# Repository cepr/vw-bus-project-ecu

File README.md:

# vw-bus-project-ecu
ECU based on Speeduino for my VW Bus project

# Licenses
The schematics and layout are under the TAPR Open Hardware License v1.0

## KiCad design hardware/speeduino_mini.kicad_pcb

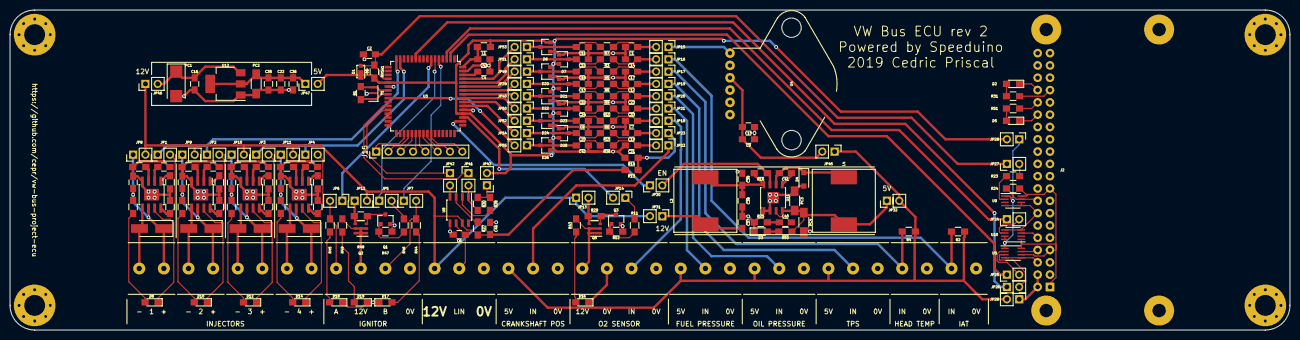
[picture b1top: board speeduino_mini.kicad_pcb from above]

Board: 2 copper layers, 264.2 x 66.0 mm, 209 parts (0 on the bottom side), 147 nets.

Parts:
C1: 0.47nF 50V; C_0805_HandSoldering
C2: 4.7nF 100V; C_0805_HandSoldering
C4, C7, C12, C14, C16, C17, C19, C21, C22, C23, C33, C35, C36, C43: 0.1uF 50V; C_0805_HandSoldering
C6: 0.22nF 200V; C_0805_HandSoldering
C8, C13, C15, C18, C20, C32, C34, C41, C42: 0.22uF 50V; C_0805_HandSoldering
C9, C39, C46: 1uF 35V; C_0805_HandSoldering
C10: 10nF 100V; C_0805_HandSoldering
C11: 0.33uF 50V; C_0805_HandSoldering
C24, C26, C28, C30: 1nF 50V; C_0805_HandSoldering
C25, C27, C29, C31: 22uF 16V; C_0805_HandSoldering
C37, C38: 22uF 25V; C_0805_HandSoldering
C40: 22nF 50V; C_0805_HandSoldering
D1: MSS1P3L-M3/89A; MicroSMP
D2, D17, D18: LED BLUE 10mA 3V; LED_0805_HandSoldering
D3, D16, D19: LED GREEN 2.5mA 2.7V; LED_0805_HandSoldering
D4: D_Schottky; D_SOD-123F
D5, D8, D10, D12, D14: LED RED 10mA 1.9V; LED_0805_HandSoldering
D6, D7, D20, D21, D22, D23, D24, D25, D26: NUP1301,215; SOT-23
D9, D11, D13, D15: B340A-13-F; D_SMA_Handsoldering
H1, H2, H3, H4: MountingHole; MountingHole_4.3mm_M4_Pad_Via
J1: O2; ED120_4DS
J2: Raspberry_Pi_2_3; RaspberryPi_uHAT
J3: TPS; ED120_3DS
J4: IAT; ED120_2DS
J5: head temperature; ED120_2DS
J6: crankshaft position sensor; ED120_3DS
J7, J8, J9, J10: Injector; ED120_2DS
J11: Ignitor Pack; ED120_4DS
J12: oil pressure; ED120_3DS
J13: fuel pressure; ED120_3DS
J14: power; ED120_3DS
J15: Conn_01x08_Female; Pin_Header_Straight_1x08_Pitch2.54mm
JP1, JP2, JP3, JP4, JP5, JP6, JP7, JP8, JP9, JP10, JP11, JP12, JP13, JP14, JP15, JP16, JP17, JP18, JP19, JP20, JP21, JP22, JP23, JP24, JP25, JP26, JP27, JP28, JP29, JP30, JP31, JP32, JP39, JP40, JP41, JP42, JP43, JP45, JP46, JP47, JP49, JP50, JP51, JP52, JP53, JP54, JP55: Jumper; Pin_Header_Straight_1x02_Pitch2.54mm
L1: 10uH; L_0805_HandSoldering
L3, L4: 47uH; BOURNS_SRR1260
PC1: 47uF; CP_Tantalum_Case-C_EIA-6032-28_Reflow
PC2, PC3, PC4: 47uF 10V; C_1206_HandSoldering
Q1, Q3: 2N7002; SOT-23
Q2, Q5: SQ3457EV; TSOP-6_1.65x3.05mm_Pitch0.95mm
R1: 1M; R_0805_HandSoldering
R2, R4: 2.49k; R_0805_HandSoldering
R3, R5, R6, R8, R9, R10, R15, R26: 470; R_0805_HandSoldering
R7: 750; R_0805_HandSoldering
R11, R23, R46: 150; R_0805_HandSoldering
R12, R16, R17, R21, R24, R29, R35, R39, R47, R48: 10k; R_0805_HandSoldering
R13: 3.9k; R_0805_HandSoldering
R14, R19, R33, R37, R41: 1k; R_0805_HandSoldering
R18, R22, R36, R40: 47.5k; R_0805_HandSoldering
R20, R34, R38, R42: 26.1k; R_0805_HandSoldering
R25: 22k; R_0805_HandSoldering
R27, R28: 33k; R_0805_HandSoldering
R30: 4k7; R_0805_HandSoldering
R31, R44, R45: 200; R_0805_HandSoldering
R43, R49: 3.74k; R_0805_HandSoldering
R50: 910; R_0805_HandSoldering
R51: 309; R_0805_HandSoldering
RN5A1: 10k; R_0805_HandSoldering
U3: ATmega2561-16AU; TQFP-64_14x14mm_Pitch0.8mm
U4: MPX4250AP1; xP_01ASB0907B
U5, U9, U10: SN74LVC2T45MDCTTEP; SSOP-8_2.95x2.8mm_Pitch0.65mm
U7, U13, U14, U15: DRV103H; TI_SO-PowerPAD-8
U8: MCP2003B; SOIC-8_3.9x4.9mm_Pitch1.27mm
U11: TLE8366; SOIC-8-1EP_3.9x4.9mm_Pitch1.27mm
U12: LD1117S50TR_SOT223; SOT-223-3_TabPin2
Y1: CSTCE16M0V53-R0; Resonator_SMD_Murata-3pin_3.2x1.3mm

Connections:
+5VA: J3.1, J6.1, J12.1, J13.1, JP29.2, JP32.2, JP45.1, R2.1, R4.1
+5VD: D1.1, D6.2, D7.2, D20.2, D21.2, D22.2, D23.2, D24.2, D25.2, D26.2, JP28.2, JP43.2, JP47.2, L1.1, RN5A1.1, U3.21, U3.52
+12V: C46.1, J14.1, JP8.2, JP9.2, JP10.2, JP11.2, JP12.2, JP13.1, JP31.2, JP46.1, R13.1, R27.2, U8.7
/Crankshaft pos sensor/IN: J6.2, JP22.1
/Fuel Pressure/IN: J13.2, JP21.1
/Head Temperature Sensor/IN: J5.1, JP17.1, R4.2
/Ignitor/+12V: JP12.1, Q2.4, R48.1
/Ignitor/EN: JP5.2, R46.2
/Ignitor/IN1: J11.1, JP6.2, R45.2
/Ignitor/IN2: J11.3, JP7.2, R44.2
/Ignitor/sheet5CF8D1B3/OUT: J11.2, Q2.1, Q2.2, Q2.5, Q2.6, R49.2
/Injector 1/+12V: C25.1, D9.1, J7.1, JP8.1, R19.1, U7.6
/Injector 1/INJ_CMD: JP1.2, R17.1, U7.8
/Injector 2/+12V: C27.1, D11.1, J8.1, JP9.1, R33.1, U13.6
/Injector 2/INJ_CMD: JP2.2, R21.1, U13.8
/Injector 3/+12V: C29.1, D13.1, J9.1, JP10.1, R37.1, U14.6
/Injector 3/INJ_CMD: JP3.2, R35.1, U14.8
/Injector 4/+12V: C31.1, D15.1, J10.1, JP11.1, R41.1, U15.6
/Injector 4/INJ_CMD: JP4.2, R39.1, U15.8
/Intake Air Temperature Sensor/IN: J4.1, JP16.1, R2.2
/MAP Sensor/+5V: C9.1, C10.1, JP45.2, U4.3
/MCU/A0: C11.1, D6.3, JP53.1, R7.1
/MCU/A1: C15.1, D7.3, JP51.1, R3.1
/MCU/A2: C18.1, D20.3, JP49.1, R5.1
/MCU/A3: C13.1, D21.3, JP39.1, R8.1
/MCU/A4: C32.1, D22.3, JP40.1, R9.1
/MCU/A5: C34.1, D23.3, JP50.1, R10.1
/MCU/A6: C8.1, D24.3, JP52.1, R6.1
/MCU/A7: C20.1, D25.3, JP54.1, R15.1
/MCU/ATMEGA regulator/AVCC: C43.1, L1.2, U3.64
/MCU/INT0: C42.1, D26.3, JP55.1, R26.1
/MCU/LIN: C6.1, J14.2, U8.6
/MCU/OC1A: JP3.1, JP4.1, U3.15
/MCU/OC1B: JP1.1, JP2.1, U3.16
/MCU/OC3A: JP7.1, U3.5
/MCU/OC3B: JP5.1, U3.6
/MCU/OC3C: JP6.1, U3.7
/MCU/PA0: JP14.2, U3.51
/MCU/PA1: JP30.1, U3.50
/MCU/RESET: C2.1, D1.2, JP27.1, RN5A1.2, U3.20
/MCU/RXD0: JP25.1, U3.2
/MCU/SCK: JP26.1, U3.11
/MCU/TXD0: JP24.1, U3.3
/MCU/sheet5D16F277/+5V: JP43.1, R28.2, R30.1
/MCU/sheet5D16F277/RXD: JP41.2, R30.2, U8.1
/MCU/sheet5D16F277/TXD: JP42.2, U8.4
/O2 Sensor Power/+12V: JP13.2, Q5.4, R29.1
/O2 Sensor Power/EN: JP14.1, R11.2
/O2 Sensor Power/OUT: J1.1, Q5.1, Q5.2, Q5.5, Q5.6, R43.2
/O2 Sensor/IN: J1.3, JP18.1
/Oil Pressure Sensor/IN: J12.2, JP20.1
/Power/+5V: JP32.1, L4.2, PC3.1, PC4.1, R50.2, U11.4
/Power/+12V: C37.1, JP31.1, L3.1
/Power/EN: JP30.2, R16.1, U11.7
/Raspberry Pi Zero W/+5VA: J2.2, J2.4, JP29.1
/Raspberry Pi Zero W/+5VD: JP28.1, U5.1, U9.1, U10.7, U10.8
/Raspberry Pi Zero W/ATMEGA_RESET: JP27.2, R23.2
/Raspberry Pi Zero W/RXD_PDO: JP24.2, U10.6
/Raspberry Pi Zero W/SCK: JP26.2, U5.3
/Raspberry Pi Zero W/TXD_PDI: JP25.2, U5.2
/Throttle Position Sensor /IN: J3.2, JP19.1
GND: C1.2, C2.2, C4.2, C6.2, C7.2, C8.2, C9.2, C10.2, C11.2, C12.2, C13.2, C14.2, C15.2, C16.2, C17.2, C18.2, C19.2, C20.2, C21.2, C22.2, C23.2, C24.2, C25.2, C26.2, C27.2, C28.2, C29.2, C30.2, C31.2, C32.2, C33.2, C34.2, C35.2, C36.2, C37.2, C38.2, C39.2, C42.2, C43.2, C46.2, D2.1, D3.1, D4.2, D5.1, D6.1, D7.1, D16.1, D17.1, D18.1, D19.1, D20.1, D21.1, D22.1, D23.1, D24.1, D25.1, D26.1, J1.2, J1.4, J2.6, J2.14, J2.20, J2.30, J2.34, J3.3, J4.2, J5.2, J6.3, J11.4, J12.3, J13.3, J14.3, PC1.2, PC2.2, PC3.2, PC4.2, Q1.2, Q3.2, R12.2, R14.2, R17.2, R18.2, R20.2, R21.2, R22.2, R25.2, R34.2, R35.2, R36.2, R38.2, R39.2, R40.2, R42.2, R47.2, U3.22, U3.53, U3.63, U4.2, U5.4, U5.5, U7.4, U7.9, U8.5, U9.4, U9.5, U9.6, U10.4, U10.5, U11.1, U11.2, U11.9, U12.1, U13.4, U13.9, U14.4, U14.9, U15.4, U15.9, Y1.2
unnamed: C1.1, JP15.2, R7.2
unnamed: C4.1, U3.62
unnamed: C7.1, JP18.2, R6.2
unnamed: C12.1, JP19.2, R8.2
unnamed: C14.1, JP16.2, R3.2
unnamed: C16.1, JP46.2, PC1.1, U12.3
unnamed: C17.1, JP17.2, R5.2
unnamed: C19.1, JP23.2, R15.2
unnamed: C21.1, JP22.2, R26.2
unnamed: C22.1, C35.1, C36.1, JP47.1, PC2.1, U12.2
unnamed: C23.1, JP20.2, R9.2
unnamed: C24.1, U7.2
unnamed: C26.1, U13.2
unnamed: C28.1, U14.2
unnamed: C30.1, U15.2
unnamed: C33.1, JP21.2, R10.2
unnamed: C38.1, C39.1, L3.2, R16.2, U11.8
unnamed: C40.1, U11.3
unnamed: C40.2, R25.1
unnamed: C41.1, U11.5
unnamed: C41.2, D4.1, L4.1, U11.6
unnamed: D2.2, R31.1
unnamed: D3.2, R50.1
unnamed: D5.2, R51.1
unnamed: D8.1, U7.7
unnamed: D8.2, R19.2
unnamed: D9.2, J7.2, U7.5
unnamed: D10.1, U13.7
unnamed: D10.2, R33.2
unnamed: D11.2, J8.2, U13.5
unnamed: D12.1, U14.7
unnamed: D12.2, R37.2
unnamed: D13.2, J9.2, U14.5
unnamed: D14.1, U15.7
unnamed: D14.2, R41.2
unnamed: D15.2, J10.2, U15.5
unnamed: D16.2, R43.1
unnamed: D17.2, R44.1
unnamed: D18.2, R45.1
unnamed: D19.2, R49.1
unnamed: J2.1, J2.17, R24.2, U5.8, U9.8, U10.1
unnamed: J2.7, U5.6
unnamed: J2.8, U5.7
unnamed: J2.10, U10.3
unnamed: J2.16, R24.1, U9.7
unnamed: J2.32, R51.2
unnamed: J2.33, R31.2
unnamed: J15.1, U3.35
unnamed: J15.2, U3.36
unnamed: J15.3, U3.37
unnamed: J15.4, U3.38
unnamed: J15.5, U3.39
unnamed: J15.6, U3.40
unnamed: J15.7, U3.41
unnamed: J15.8, U3.42
unnamed: JP15.1, U4.1
unnamed: JP23.1, R13.2, R14.1
unnamed: JP39.2, U3.58
unnamed: JP40.2, U3.57
unnamed: JP41.1, U3.27
unnamed: JP42.1, U3.28
unnamed: JP49.2, U3.59
unnamed: JP50.2, U3.56
unnamed: JP51.2, U3.60
unnamed: JP52.2, U3.55
unnamed: JP53.2, U3.61
unnamed: JP54.2, U3.54
unnamed: JP55.2, U3.25
unnamed: Q1.1, R46.1, R47.1
unnamed: Q1.3, Q2.3, R48.2
unnamed: Q3.1, R11.1, R12.1
unnamed: Q3.3, Q5.3, R29.2
unnamed: R1.1, U3.24, Y1.1
unnamed: R1.2, U3.23, Y1.3
unnamed: R18.1, U7.3
unnamed: R20.1, U7.1
unnamed: R22.1, U13.3
unnamed: R23.1, U9.2
unnamed: R27.1, U8.3
unnamed: R28.1, U8.2
unnamed: R34.1, U13.1
unnamed: R36.1, U14.3
unnamed: R38.1, U14.1
unnamed: R40.1, U15.3
unnamed: R42.1, U15.1

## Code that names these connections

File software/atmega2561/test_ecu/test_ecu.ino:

#define INJECTOR_12           12 // OC1B / PB6
#define INJECTOR_34           11 // OC1A / PB5
#define IGNITOR_EN             3 // OC3B / PE4
#define IGNITOR_IN1            2 // OC3C / PE5
#define IGNITOR_IN2            5 // OC3A / PE3
#define POWER_EN              23 // PA1
#define FUEL_PRESSURE         A5 // A5
#define OIL_PRESSURE          A4
#define CRANKSHAFT_POS_SENSOR 21 // INT0 / PD0
#define VBAT                  A7
#define HEAD_TEMP             A2
#define INTAKE_AIR_TEMP       A1
#define TPS                   A3
#define MAP                   A0
#define O2_SENSOR             A6
#define O2_SENSOR_EN          22 // PA0

void setup() {
  pinMode(INJECTOR_12, OUTPUT);
  digitalWrite(INJECTOR_12, LOW);

  pinMode(INJECTOR_34, OUTPUT);
  digitalWrite(INJECTOR_34, LOW);

  pinMode(IGNITOR_EN, OUTPUT);
  digitalWrite(IGNITOR_EN, LOW);

  pinMode(IGNITOR_IN1, OUTPUT);
  digitalWrite(IGNITOR_IN1, LOW);

  pinMode(IGNITOR_IN2, OUTPUT);
  digitalWrite(IGNITOR_IN2, LOW);

  pinMode(POWER_EN, INPUT);

  pinMode(CRANKSHAFT_POS_SENSOR, INPUT_PULLUP);

  pinMode(O2_SENSOR_EN, OUTPUT);
  digitalWrite(O2_SENSOR_EN, LOW);

  Serial.begin(115200);
}

void loop() {
  while (Serial.available()) {
    char received = Serial.read();
    Serial.write(received);
    if (received == 'S') {
      pinMode(POWER_EN, OUTPUT);
      digitalWrite(POWER_EN, LOW);
    } else if (received == 'R') {
      pinMode(POWER_EN, OUTPUT);
      digitalWrite(POWER_EN, LOW);
      delay(1000);
      pinMode(POWER_EN, INPUT);
    } else if (received == '1') {
      digitalWrite(INJECTOR_12, HIGH);
      delay(1000);
      digitalWrite(INJECTOR_12, LOW);
    } else if (received == '2') {
      digitalWrite(INJECTOR_34, HIGH);
      delay(1000);
      digitalWrite(INJECTOR_34, LOW);
    } else if (received == '3') {
      digitalWrite(IGNITOR_EN, HIGH);
    } else if (received == '4') {
      digitalWrite(IGNITOR_IN1, HIGH);
    } else if (received == '5') {
      digitalWrite(IGNITOR_IN2, HIGH);
    } else if (received == '6') {
      digitalWrite(O2_SENSOR_EN, HIGH);
    }
  }
}

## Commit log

2019-02-18 Work in progress
2019-02-26 work in progress - components ordered
2019-03-17 rev 1
2019-04-10 rev 1.1
2019-04-18 Adding corrections for wrong raspberry pi pinout
2019-05-19 Rev 2 work in progress
2019-05-21 hardware rev2 - layout complete
2019-05-30 rev 2 sent to fab
2019-06-16 Moved PC3, fixed R25, D3, C40 and R50 silkscreen
2020-10-24 old commit from v1
